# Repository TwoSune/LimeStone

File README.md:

# LimeStone
Limestone is a revision/iteration of Marksard's Rhymestone. You can see the original here: https://github.com/marksard/Keyboards/tree/master/rhymestone

Currently, there is no build guide, but feel free to make one and push to the repository if you want to!

You can find the firmware here: https://github.com/TwoSune/Rhymestone2-Firmware

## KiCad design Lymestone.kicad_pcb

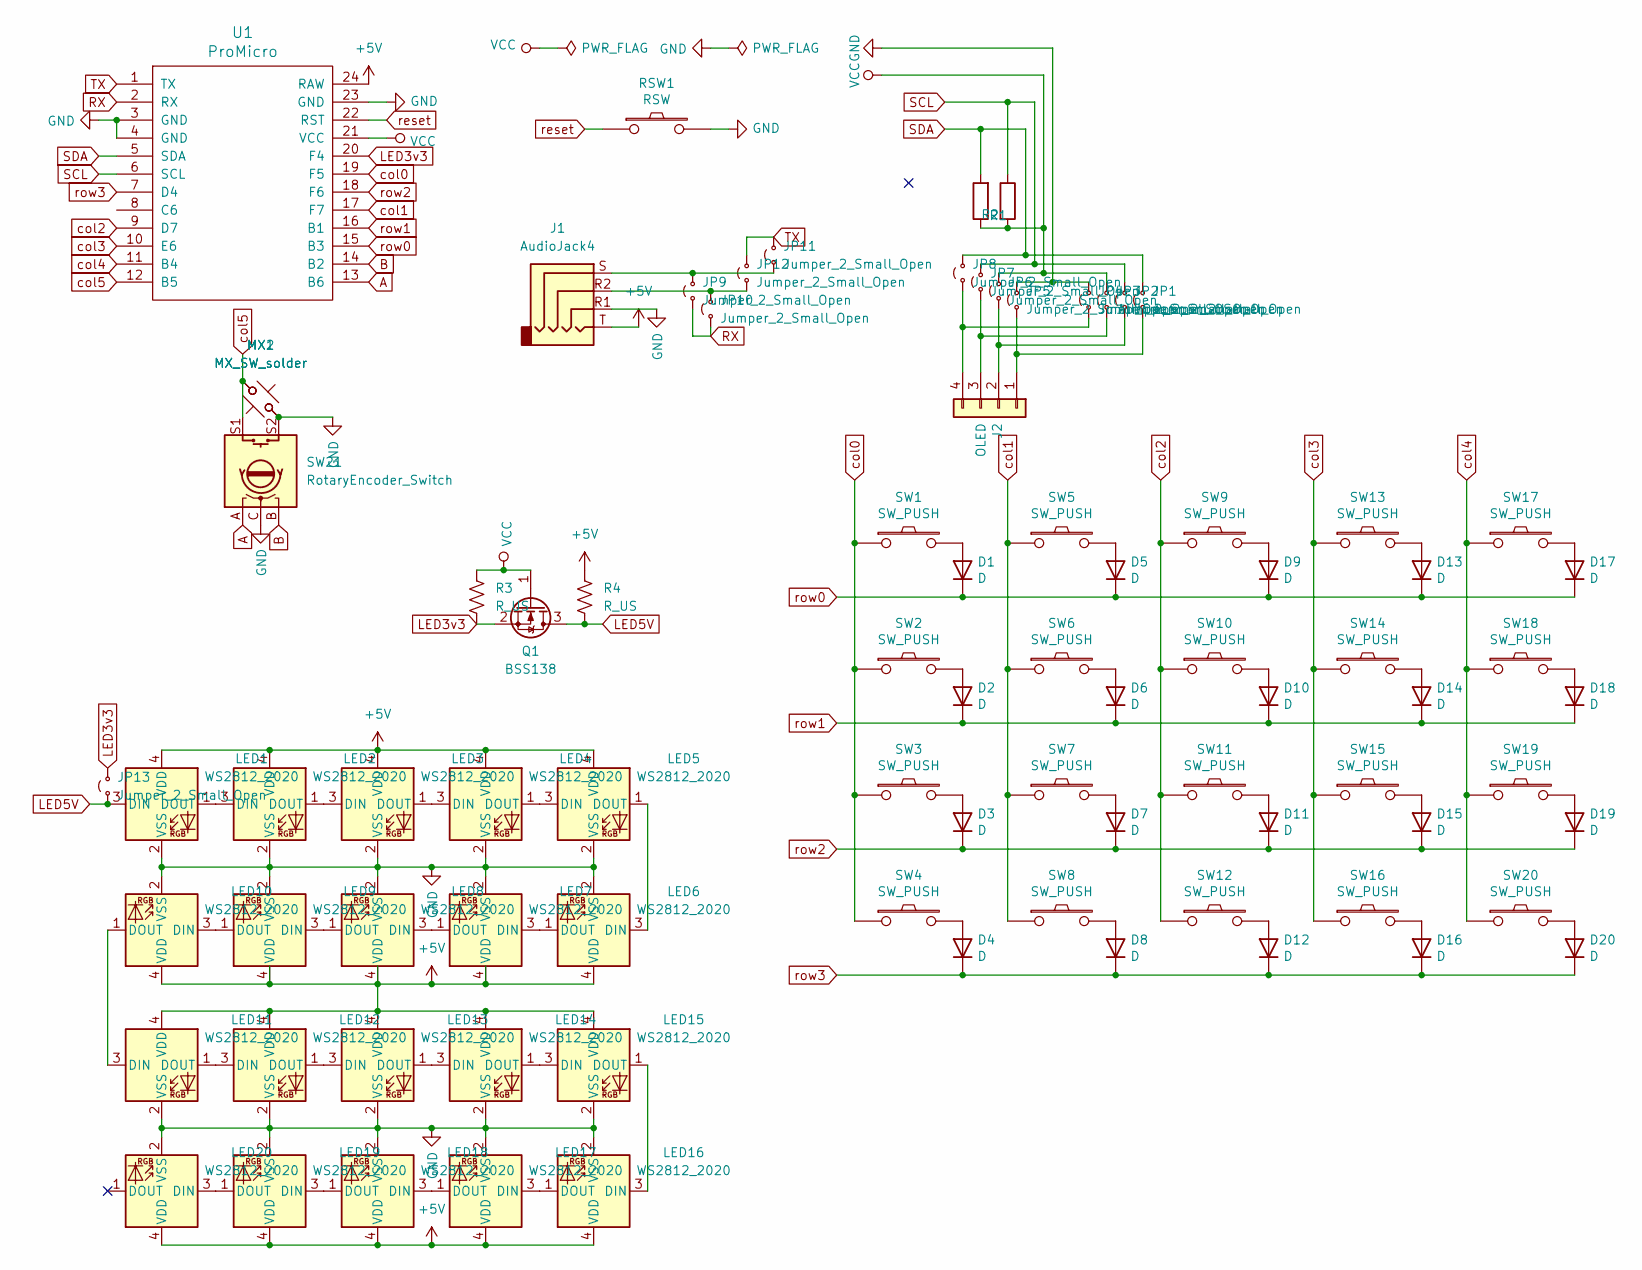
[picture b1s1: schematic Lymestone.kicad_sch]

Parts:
D1, D2, D3, D4, D5, D6, D7, D8, D9, D10, D11, D12, D13, D14, D15, D16, D17, D18, D19, D20: D; D3_SMD
J1: AudioJack4; CON_MJ-4PP-9_Reversible
J2: OLED; PinHeader_1x04_P2.54mm_Vertical
JP1, JP2, JP3, JP4, JP5, JP6, JP7, JP8, JP9, JP10, JP11, JP12: Jumper_2_Small_Open; SolderJumper-2_P1.3mm_Open_RoundedPad1.0x1.5mm
JP13: Jumper_2_Small_Open; SolderJumper-2_P1.3mm_Open_Pad1.0x1.5mm
LED1, LED2, LED3, LED4, LED5, LED6, LED7, LED8, LED9, LED10, LED11, LED12, LED13, LED14, LED15, LED16, LED17, LED18, LED19, LED20: WS2812_2020; LED_WS2812_2020_rearmount_reversible
MX1, MX2: MX_SW_solder; SW_MX_1u
Q1: BSS138; SOT-23
R1, R2: R; R_Axial_DIN0207_L6.3mm_D2.5mm_P7.62mm_Horizontal
R3, R4: R_US; R_0805_2012Metric
RSW1: RSW; ResetSW
SW1, SW2, SW3, SW4, SW5, SW6, SW7, SW8, SW9, SW10, SW11, SW12, SW13, SW14, SW15, SW16, SW17, SW18, SW19, SW20: SW_PUSH; CherryMX_Hotswap
SW21: RotaryEncoder_Switch; ROT_Alps_EC11E-Switch
U1: ProMicro; ProMicro_v2

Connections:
+5V: J1.T, LED1.4 (VDD), LED2.4 (VDD), LED3.4 (VDD), LED4.4 (VDD), LED5.4 (VDD), LED6.4 (VDD), LED7.4 (VDD), LED8.4 (VDD), LED9.4 (VDD), LED10.4 (VDD), LED11.4 (VDD), LED12.4 (VDD), LED13.4 (VDD), LED14.4 (VDD), LED15.4 (VDD), LED16.4 (VDD), LED17.4 (VDD), LED18.4 (VDD), LED19.4 (VDD), LED20.4 (VDD), R4.1, U1.24 (RAW)
A: SW21.A, U1.13 (B6)
B: SW21.B, U1.14 (B2)
GND: J1.R1, JP4.2 (B), JP5.2 (B), LED1.2 (VSS), LED2.2 (VSS), LED3.2 (VSS), LED4.2 (VSS), LED5.2 (VSS), LED6.2 (VSS), LED7.2 (VSS), LED8.2 (VSS), LED9.2 (VSS), LED10.2 (VSS), LED11.2 (VSS), LED12.2 (VSS), LED13.2 (VSS), LED14.2 (VSS), LED15.2 (VSS), LED16.2 (VSS), LED17.2 (VSS), LED18.2 (VSS), LED19.2 (VSS), LED20.2 (VSS), MX1.2, MX2.1, RSW1.2, SW21.C, SW21.S2, U1.3 (GND), U1.4 (GND), U1.23 (GND)
LED3v3: JP13.2 (B), Q1.2 (S), R3.2, U1.20 (F4)
LED5V: JP13.1 (A), LED1.3 (DIN), Q1.3 (D), R4.2
unnamed: D1.2 (A), SW1.2
unnamed: D2.2 (A), SW2.2
unnamed: D3.2 (A), SW3.2
unnamed: D4.2 (A), SW4.2
unnamed: D5.2 (A), SW5.2
unnamed: D6.2 (A), SW6.2
unnamed: D7.2 (A), SW7.2
unnamed: D8.2 (A), SW8.2
unnamed: D9.2 (A), SW9.2
unnamed: D10.2 (A), SW10.2
unnamed: D11.2 (A), SW11.2
unnamed: D12.2 (A), SW12.2
unnamed: D13.2 (A), SW13.2
unnamed: D14.2 (A), SW14.2
unnamed: D15.2 (A), SW15.2
unnamed: D16.2 (A), SW16.2
unnamed: D17.2 (A), SW17.2
unnamed: D18.2 (A), SW18.2
unnamed: D19.2 (A), SW19.2
unnamed: D20.2 (A), SW20.2
unnamed: J2.1, JP1.1 (A), JP5.1 (A)
unnamed: J2.2, JP2.1 (A), JP6.1 (A)
unnamed: J2.3, JP3.1 (A), JP7.1 (A)
unnamed: J2.4, JP4.1 (A), JP8.1 (A)
unnamed: J1.R2, JP10.2 (B), JP12.1 (A)
unnamed: J1.S, JP9.2 (B), JP11.1 (A)
unnamed: LED1.1 (DOUT), LED2.3 (DIN)
unnamed: LED2.1 (DOUT), LED3.3 (DIN)
unnamed: LED3.1 (DOUT), LED4.3 (DIN)
unnamed: LED4.1 (DOUT), LED5.3 (DIN)
unnamed: LED5.1 (DOUT), LED6.3 (DIN)
unnamed: LED6.1 (DOUT), LED7.3 (DIN)
unnamed: LED7.1 (DOUT), LED8.3 (DIN)
unnamed: LED8.1 (DOUT), LED9.3 (DIN)
unnamed: LED9.1 (DOUT), LED10.3 (DIN)
unnamed: LED10.1 (DOUT), LED11.3 (DIN)
unnamed: LED11.1 (DOUT), LED12.3 (DIN)
unnamed: LED12.1 (DOUT), LED13.3 (DIN)
unnamed: LED13.1 (DOUT), LED14.3 (DIN)
unnamed: LED14.1 (DOUT), LED15.3 (DIN)
unnamed: LED15.1 (DOUT), LED16.3 (DIN)
unnamed: LED16.1 (DOUT), LED17.3 (DIN)
unnamed: LED17.1 (DOUT), LED18.3 (DIN)
unnamed: LED18.1 (DOUT), LED19.3 (DIN)
unnamed: LED19.1 (DOUT), LED20.3 (DIN)
RX: JP9.1 (A), JP10.1 (A), U1.2 (RX)
SCL: JP2.2 (B), JP7.2 (B), R2.1, U1.6 (SCL)
SDA: JP1.2 (B), JP8.2 (B), R1.2, U1.5 (SDA)
TX: JP11.2 (B), JP12.2 (B), U1.1 (TX)
VCC: JP3.2 (B), JP6.2 (B), Q1.1 (G), R1.1, R2.2, R3.1, U1.21 (VCC)
col0: SW1.1, SW2.1, SW3.1, SW4.1, U1.19 (F5)
col1: SW5.1, SW6.1, SW7.1, SW8.1, U1.17 (F7)
col2: SW9.1, SW10.1, SW11.1, SW12.1, U1.9 (D7)
col3: SW13.1, SW14.1, SW15.1, SW16.1, U1.10 (E6)
col4: SW17.1, SW18.1, SW19.1, SW20.1, U1.11 (B4)
col5: MX1.1, MX2.2, SW21.S1, U1.12 (B5)
reset: RSW1.1, U1.22 (RST)
row0: D1.1 (K), D5.1 (K), D9.1 (K), D13.1 (K), D17.1 (K), U1.15 (B3)
row1: D2.1 (K), D6.1 (K), D10.1 (K), D14.1 (K), D18.1 (K), U1.16 (B1)
row2: D3.1 (K), D7.1 (K), D11.1 (K), D15.1 (K), D19.1 (K), U1.18 (F6)
row3: D4.1 (K), D8.1 (K), D12.1 (K), D16.1 (K), D20.1 (K), U1.7 (D4)

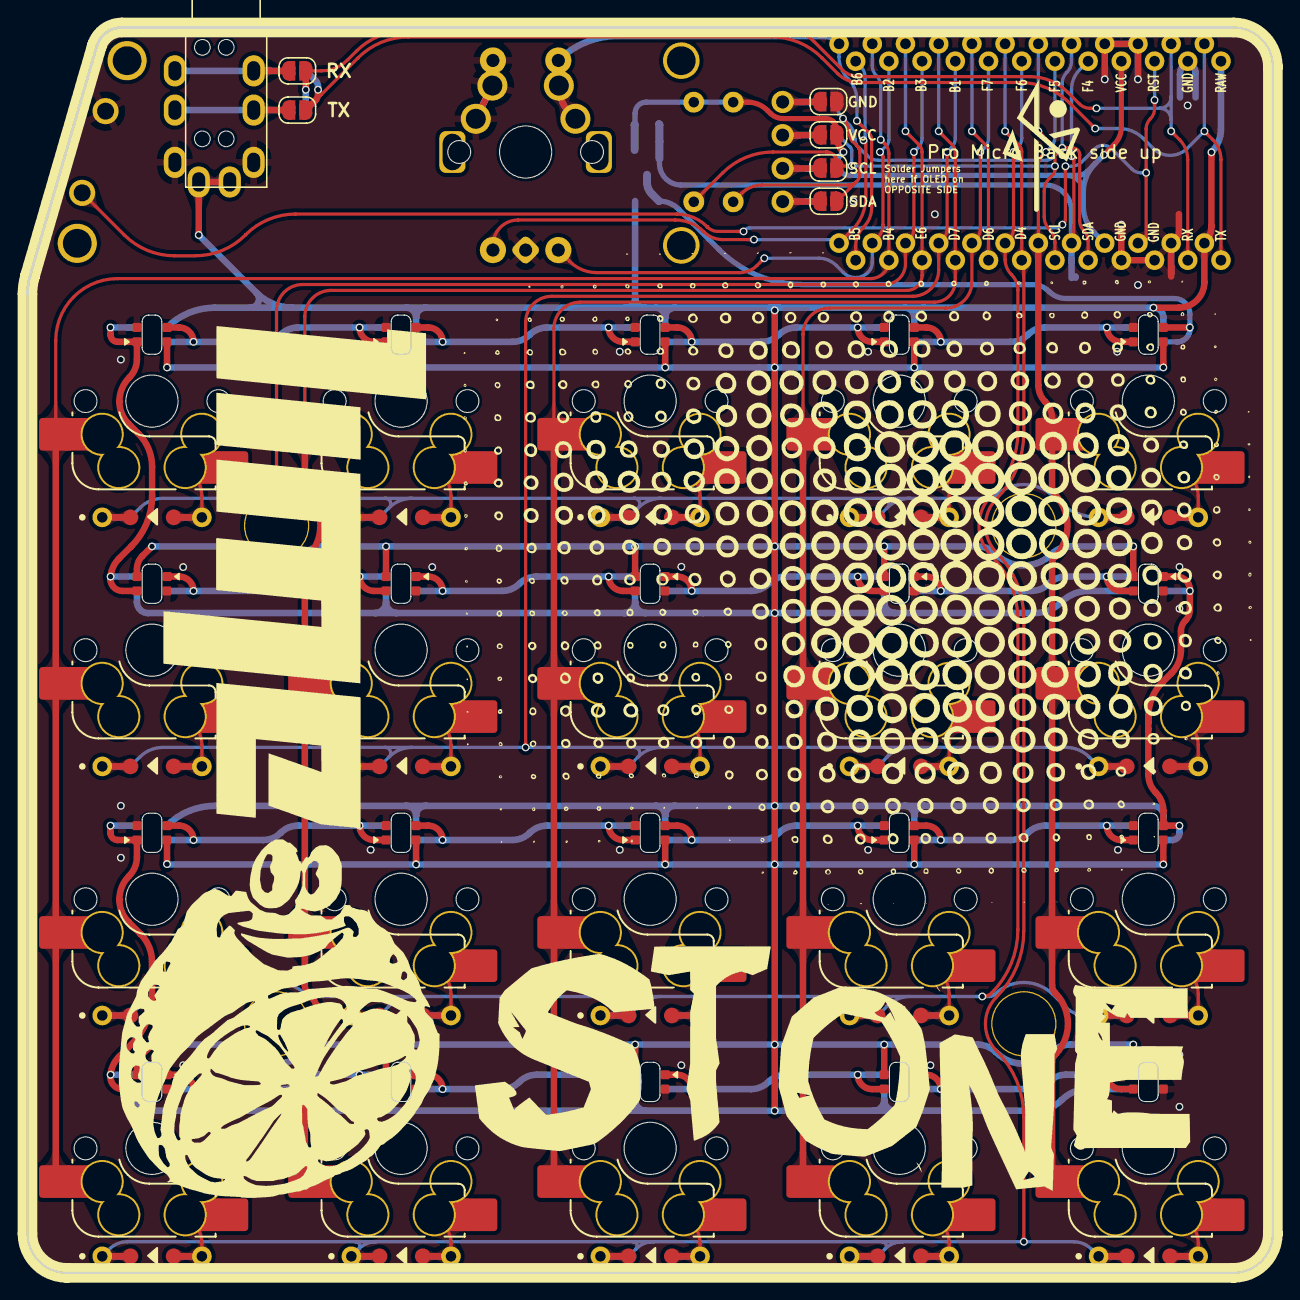
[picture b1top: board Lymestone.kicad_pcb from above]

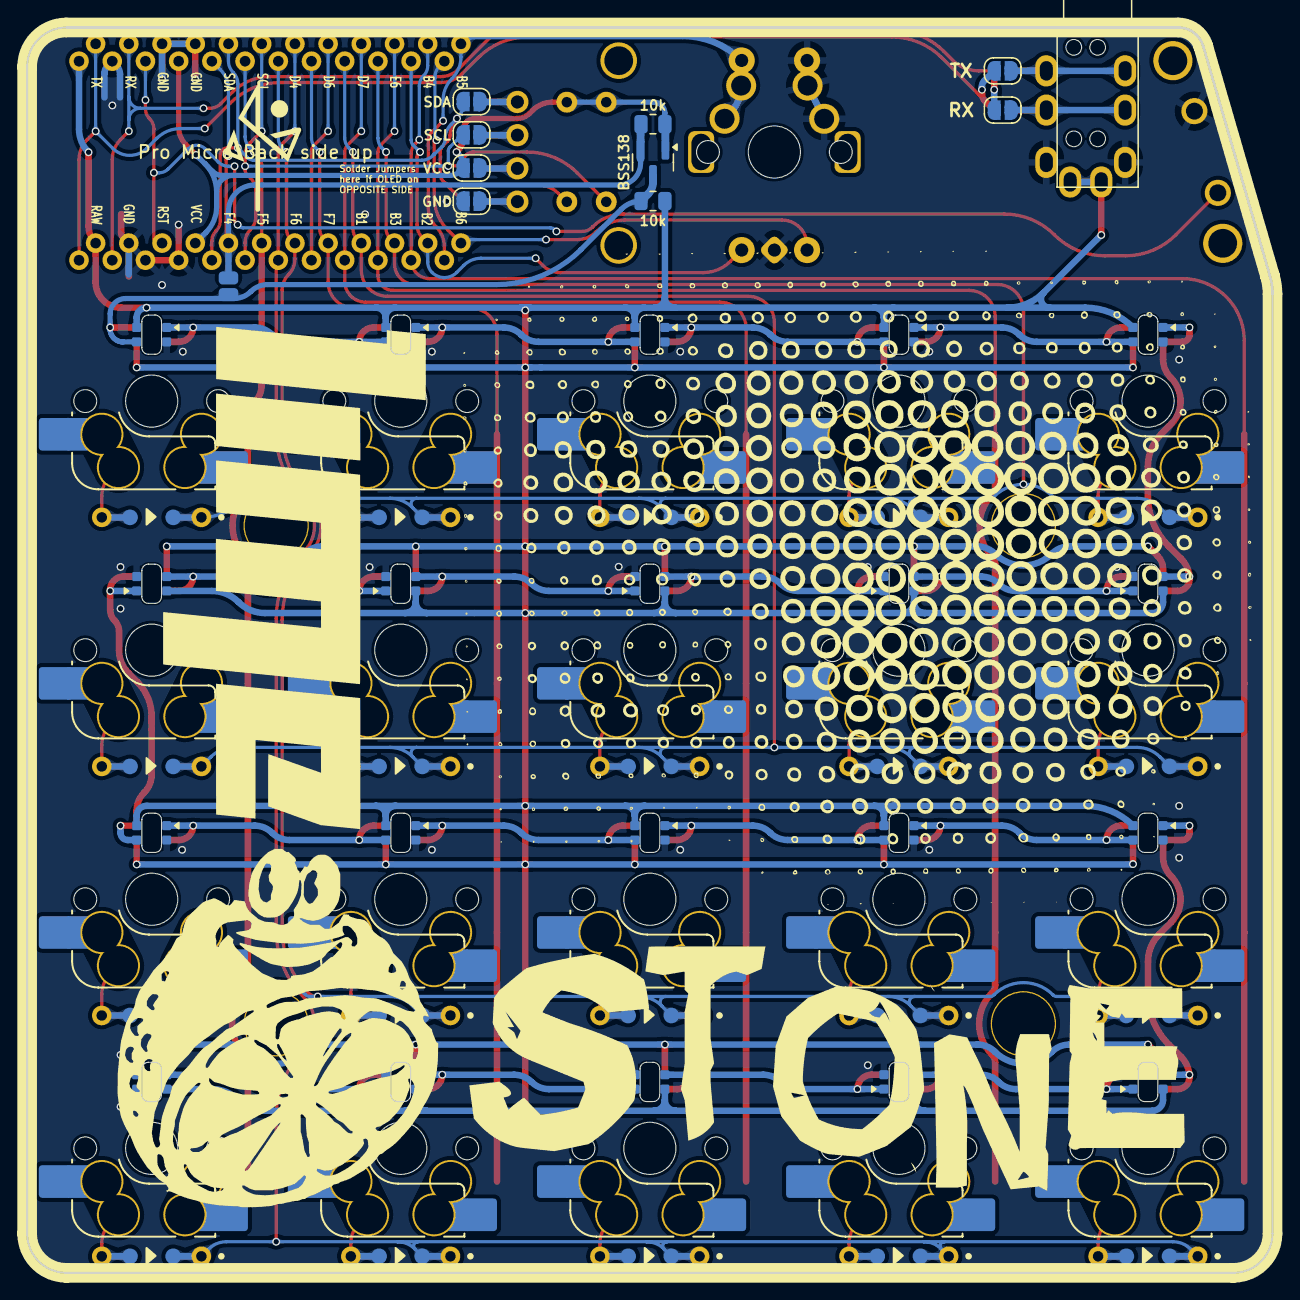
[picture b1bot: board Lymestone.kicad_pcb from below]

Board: 2 copper layers, 95.2 x 95.3 mm, 91 parts (21 on the bottom side), 67 nets.

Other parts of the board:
h1, h2, h3, h4: hole; LEGO_HOLE
h7, h8: hole; LEGO_HOLE2
